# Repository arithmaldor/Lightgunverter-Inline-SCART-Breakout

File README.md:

# Lightgunverter Inline SCART Breakout
Using this [4 position jack](https://www.arrow.com/en/products/sj-43514-smt-tr/cui-inc) and a standard 3.5mm 4 pole to Yellow, White, Red RCA jacks, you can put this in between your SCART cable and the destination to break out green for the overlay and sync.
Yellow is sync, white goes to the "Video In" jack, and Red goes to the "Video Out" jack.

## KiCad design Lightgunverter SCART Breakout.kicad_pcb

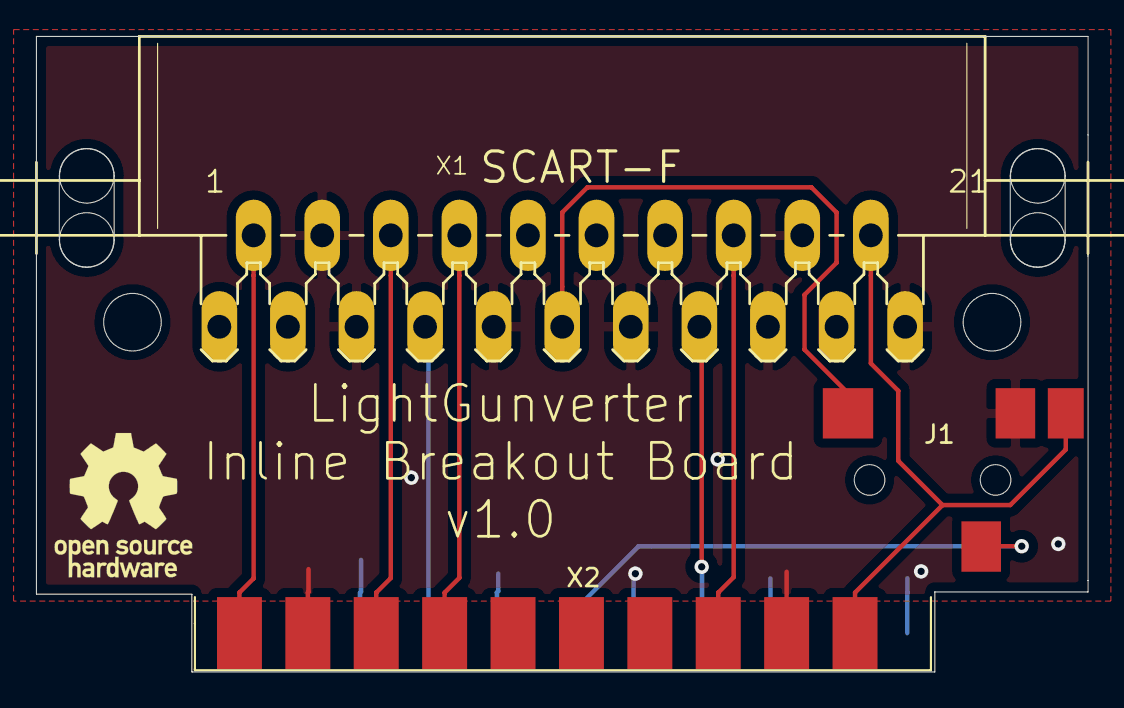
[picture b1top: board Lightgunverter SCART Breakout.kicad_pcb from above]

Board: 2 copper layers, 58.4 x 35.3 mm, 3 parts (0 on the bottom side), 10 nets.

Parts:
J1: AudioJack4; 4POS_JACK
X1: SCART-F
X2: SCART-F; MALE_SCART

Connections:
BLANKING: X1.16, X2.16
BLUE: X1.7, X2.7
GND: J1.4, X1.4, X1.5, X1.9, X1.13, X1.17, X1.18, X1.21, X2.4, X2.5, X2.9, X2.13, X2.17, X2.18, X2.21
GREEN_IN: J1.2, X1.11
GREEN_OUT: J1.3, X2.11
LEFT: X1.6, X2.6
RED: X1.15, X2.15
RIGHT: X1.2, X2.2
SWITCH: X1.8, X2.8
SYNC: J1.1, X1.20, X2.20

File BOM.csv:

QTY,REF,DESC,LINK
1,X1,FEMALE SCART,https://console5.com/store/female-scart-jp21-through-hole-pc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
1,X2,MALE SCART,https://console5.com/store/scart-plug-21-pin-male-cable-conn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
1,J1,4POS 3.5mm Jack,https://www.arrow.com/en/products/sj-43514-smt-tr/cui-inc

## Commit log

2019-04-07 Moved files into folder. Initial commit
2019-06-12 Moved silkscreen title
    Moved the name of the board so it wouldn't be covered by the 3.5mm jack

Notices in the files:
Lightgunverter SCART Breakout.kicad_pcb:
Licensed under CERN OHL 1.2
